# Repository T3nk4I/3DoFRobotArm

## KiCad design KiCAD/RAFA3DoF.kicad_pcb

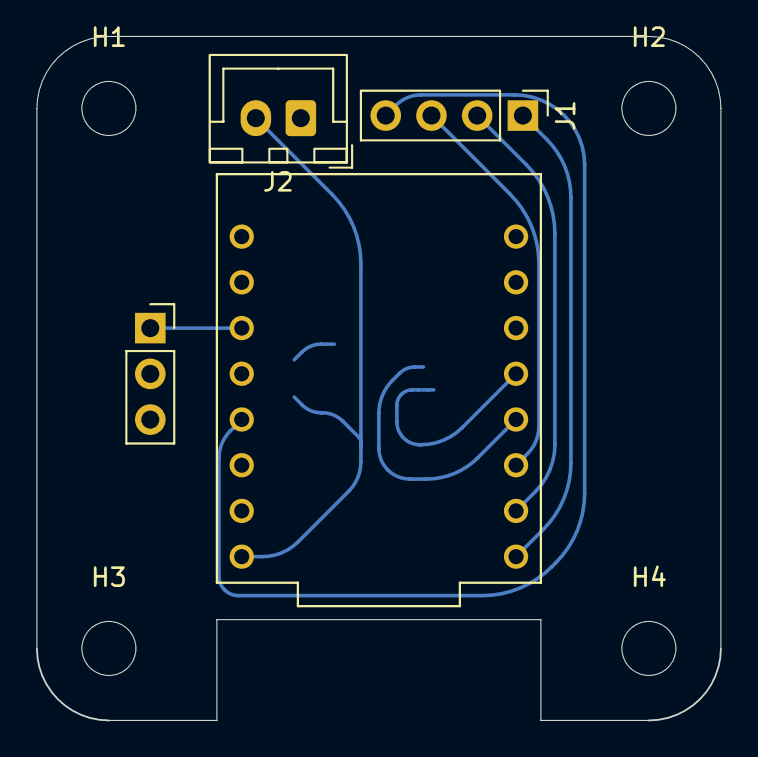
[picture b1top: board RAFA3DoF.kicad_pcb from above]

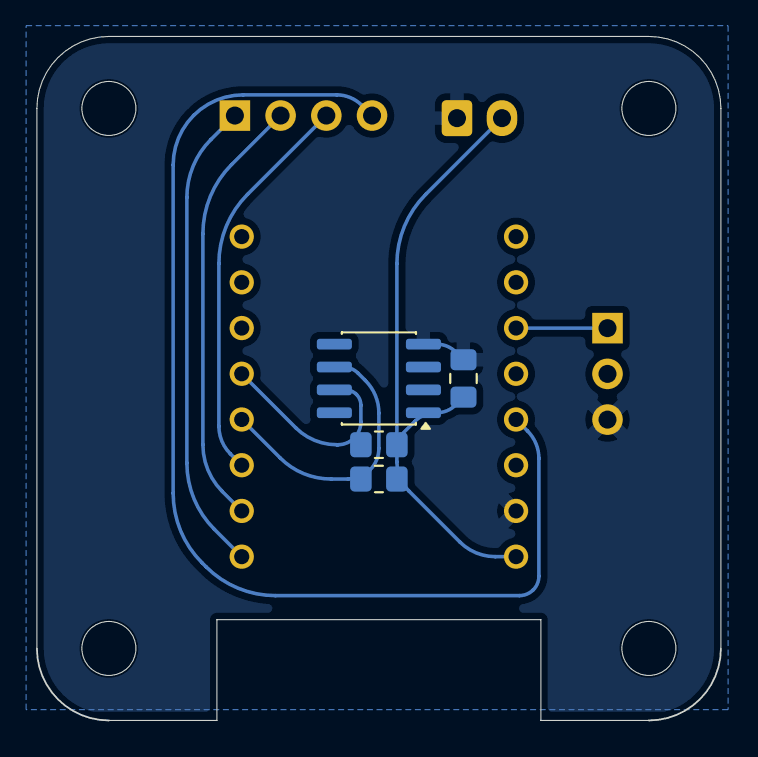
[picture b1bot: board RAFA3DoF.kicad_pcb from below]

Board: 2 copper layers, 38.0 x 38.0 mm, 12 parts (4 on the bottom side), 9 nets.

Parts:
C2: 100nF; C_0805_2012Metric_Pad1.18x1.45mm_HandSolder
H1, H2, H3, H4: MountingHole; MountingHole_3mm
IC1: AS5600-ASOT; SOIC-8_3.9x4.9mm_P1.27mm
J1: Conn_01x04; PinHeader_1x04_P2.54mm_Vertical
J2: Conn_01x02; JST_XH_B2B-XH-A_1x02_P2.50mm_Vertical
J3: Conn_01x03; PinSocket_1x03_P2.54mm_Vertical
R1, R2: 4.7k; R_0805_2012Metric_Pad1.20x1.40mm_HandSolder
U1: ESP32-C3_SUPERMINI_SMD; MODULE_ESP32-C3_SUPERMINI_TH

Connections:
5V: C2.1, IC1.1 (VDD5V), J2.2, R1.1, R2.1, U1.5V
/MISO: J1.1, U1.5 (GPIO5)
/MOSI: J1.2, U1.6 (GPIO6)
/PWM: J3.1, U1.2 (GPIO2)
/SCK: J1.4, U1.4 (GPIO4)
/SCL: IC1.6 (SDA), R2.2, U1.8 (GPIO8)
/SDA: IC1.7 (SCL), R1.2, U1.9 (GPIO9)
/SS: J1.3, U1.7 (GPIO7)
GND: C2.2, IC1.4 (GND), J2.1, J3.3, U1.G (GND)

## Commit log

2024-07-01 Created new repo
2024-07-01 updates funcionality of main control program
2026-06-12 uploads Kicad files for the encoder-motor control unit
2026-06-12 created new folder to store KiCAD files
2026-06-13 Chenges traces to rounded ones
